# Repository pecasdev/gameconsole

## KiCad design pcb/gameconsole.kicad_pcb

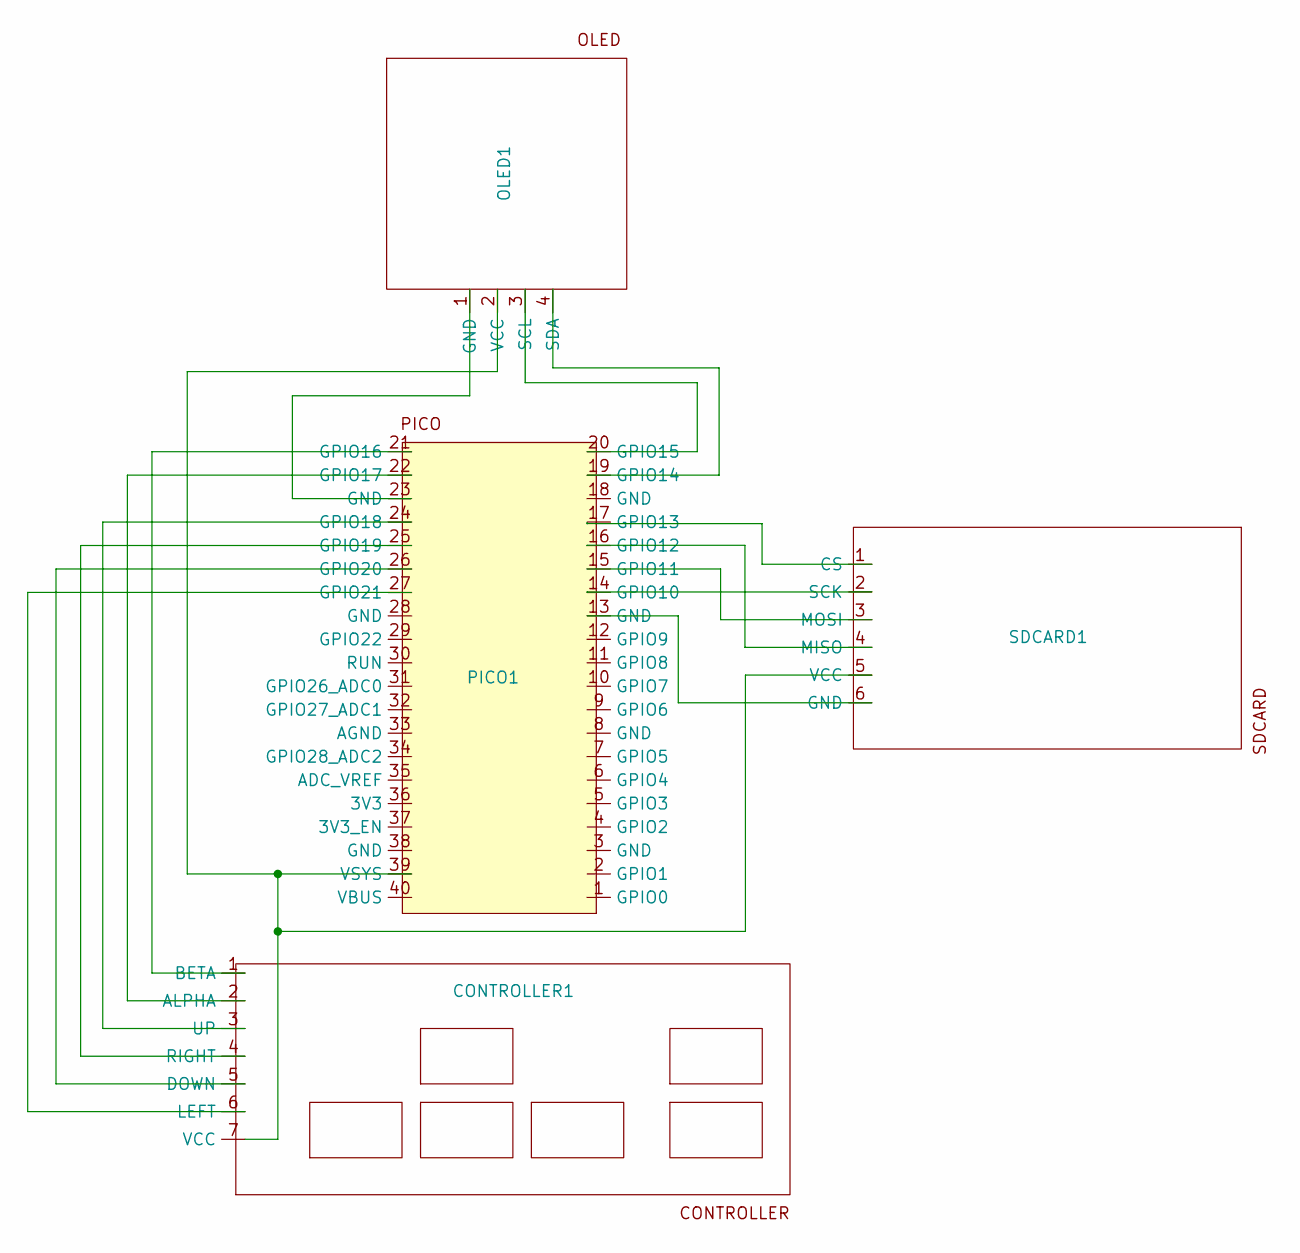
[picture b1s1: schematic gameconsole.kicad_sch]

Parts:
CONTROLLER1: controller_mount
OLED1: oled
PICO1: pico
SDCARD1: sdcard

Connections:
unnamed: CONTROLLER1.2 (ALPHA), PICO1.22 (GPIO17)
unnamed: CONTROLLER1.1 (BETA), PICO1.21 (GPIO16)
unnamed: CONTROLLER1.5 (DOWN), PICO1.26 (GPIO20)
unnamed: CONTROLLER1.6 (LEFT), PICO1.27 (GPIO21)
unnamed: CONTROLLER1.4 (RIGHT), PICO1.25 (GPIO19)
unnamed: CONTROLLER1.3 (UP), PICO1.24 (GPIO18)
unnamed: CONTROLLER1.7 (VCC), OLED1.2 (VCC), PICO1.39 (VSYS), SDCARD1.5 (VCC)
unnamed: OLED1.1 (GND), PICO1.23 (GND)
unnamed: OLED1.3 (SCL), PICO1.20 (GPIO15)
unnamed: OLED1.4 (SDA), PICO1.19 (GPIO14)
unnamed: PICO1.14 (GPIO10), SDCARD1.2 (SCK)
unnamed: PICO1.15 (GPIO11), SDCARD1.3 (MOSI)
unnamed: PICO1.16 (GPIO12), SDCARD1.4 (MISO)
unnamed: PICO1.17 (GPIO13), SDCARD1.1 (CS)
unnamed: PICO1.13 (GND), SDCARD1.6 (GND)

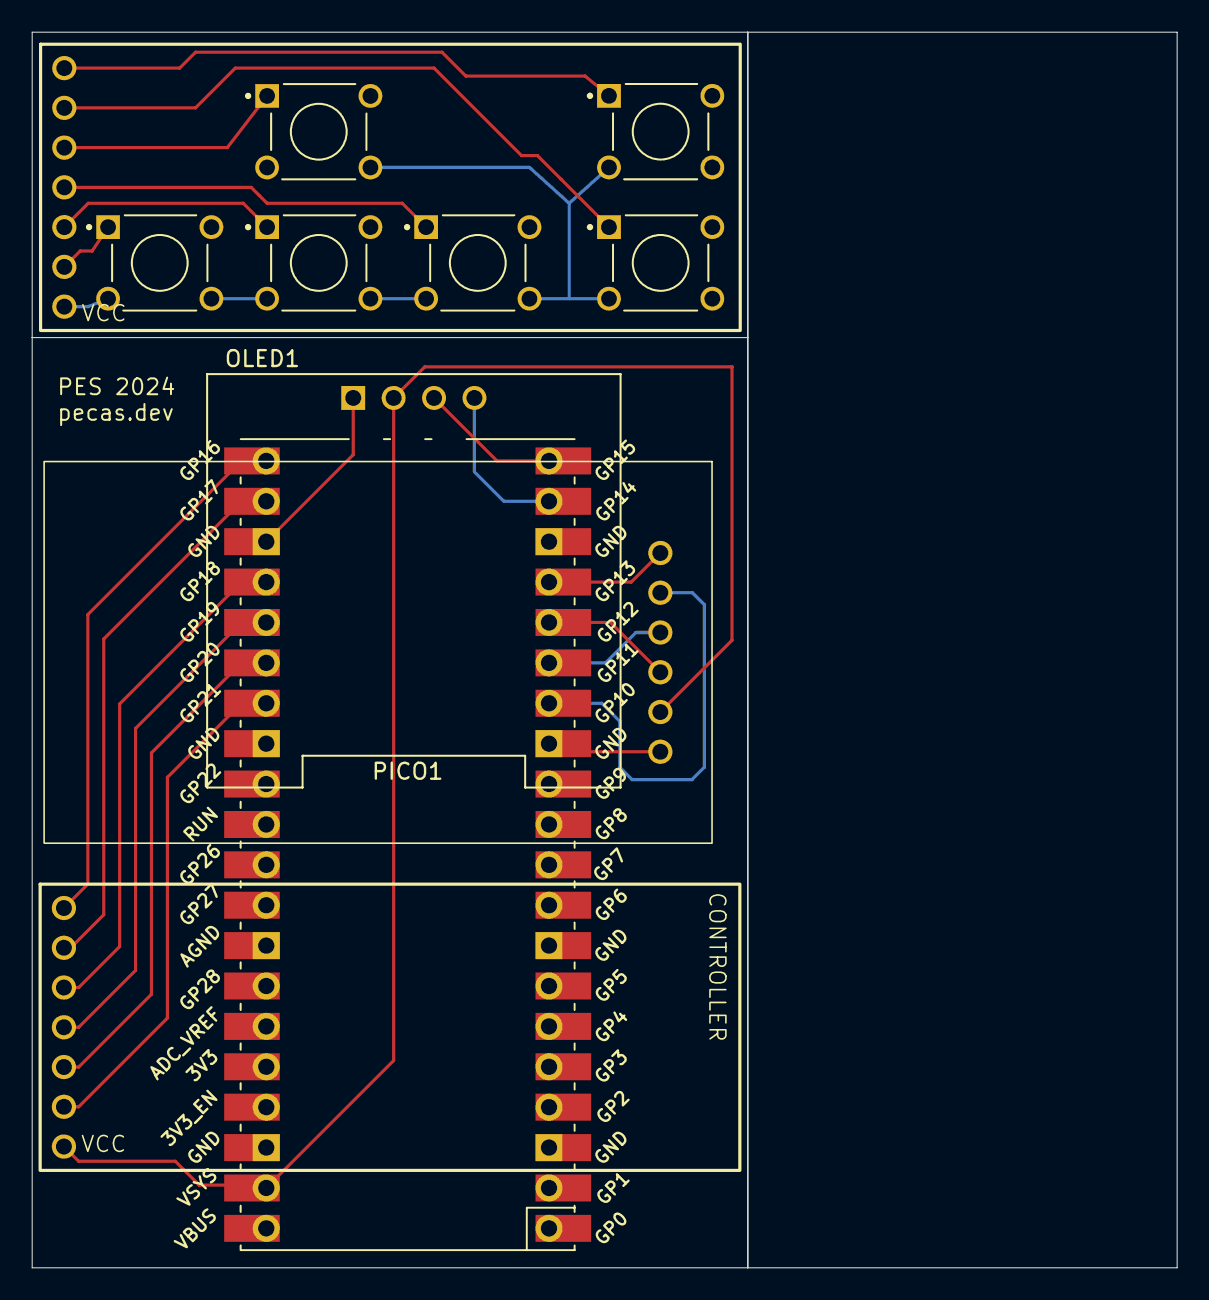
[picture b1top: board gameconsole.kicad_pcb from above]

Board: 2 copper layers, 72.0 x 77.7 mm, 5 parts (0 on the bottom side), 15 nets.

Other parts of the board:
U: controller

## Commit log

2024-07-15 Initial commit
    A dump of assorted files from last weekend's hackathon
2024-07-18 Remove individual inject folders
    Will move this to the root directory. Also moved original inject to examples folder
2024-07-18 Add snake to inject
2024-07-18 Create root init
    The plans for this is to have the emulator be the one-stop-shop for everything gameconsole. You can use it to flash the hardware or emulate the injection.
2024-07-18 Add flash_to_pico
2024-07-18 Remove draw_text from screen
    Font is currently handling this. Idk if this is the right way to implement it, I'll probably change it later
2024-07-18 Rewrite library
    - Engine has been made into a global object for ease of use
    - Some variables were made "private"
2024-07-18 Rewrite emulate button handling
    Button handling was heavily changed to try and speed up the emulator but there is still a noticable ~40ms delay that is not present on the hardware.
    Also inputs get occasionally dropped but I spent too much time on this to fix it. It's like 90% good now and it'll take 10 hours to get that last 10% so it's not a priority.
2024-07-18 Rename hardware __init__ -> main
    This is what pico uses so this change makes the naming more consistent
2024-07-18 Remove hardware debug statements
2024-07-19 Rewrite font
    Font should be way easier to use now. I also rewrote the font tool to match.
2024-07-19 Add InjectSelectMenu
    This will only be present in the hardware side. It gives the user the ability to choose what injection to load from the sd card
2024-07-19 Rewrite Font
2024-07-19 Move reaction example back to inject folder
    It should technically remain in the examples folder but I don't want 2 versions of the same code lingering around so I'll move it back to examples when I'm done
    I also added a small sprite usecase for the reaction game
2024-07-23 Rewrite reaction
    Now featuring new and improved sprites!
2024-07-23 Move font importing for emulation
2024-07-23 Add limitations
    I may update this later with my findings
2024-07-23 Remove pygame driver tick
    Since engine is doing tick capping, we don't need the pygame implementation
2024-07-23 Add button test example
2024-07-23 Add "professional" printing to main2
2024-07-23 Ignore more folders
    Tool input/output folders will be ignored. I think the inject folder should also be ignored just based on how frequently I update it. For the final version, I might put some dummy starter code there 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
2024-07-23 Add Alarm
2024-07-23 Rename v -> bitmap
2024-07-23 Improve injection copying
    Injection copying should now work recursively for nested folders and it should retry if copying fails (sometimes it does)
2024-07-23 Add FrameBufferAdaptor
    This only really exists so that sprites can be more efficiently drawn (the previous method took 5 seconds to blit on hardware)
2024-07-23 Untrack previously tracked files
2024-07-23 Fix HardwareState resetting
    This file is kind of a mess. I hope the convenience of a global variable is worth it
2024-07-23 Add "-" to font
    This replaces whatever godforsaken character I had in the bottom right before
2024-07-23 Change sprite_convert to strip extension when saving a sprite
2024-07-25 Reimplement pygame for emulator tick
    Apparently pygame doesn't like time.sleep
2024-07-25 Fix circular imports
    Python doesn't let you import a class to use for typing if that class imports the thing you're defining the type in (circular import). I almost miss java. I think there's a fix for this that involves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
2024-07-25 Add objects_of_class to Engine
2024-07-25 Rewrite snake
2024-07-29 Fix whitespace
2024-07-29 Fix import issues
2024-07-29 Fix tools module
2024-08-20 Rewrite __init__ to support tool scripts
2024-08-20 Add clear_pixel to Screen
2024-08-20 Add pcb files
2024-08-20 Make copy_file function safer
2024-08-20 Add returns to engine API
2024-08-20 Add util functions
2024-08-20 Add inject_select_menu
2024-08-20 Move hardware button pins to other side of pico
    Makes the PCB easier to engineer
2024-08-20 Add sprite loading
    This is mostly a hardware thing, it's to load spritedata into memory
2024-08-21 Add Tetris injection
2024-08-21 Rename examples -> published_injections
2024-08-21 Add flash_to_sd
2024-08-21 Fix sprite loading in reaction
2024-08-21 Clean up imports + comments
2024-08-27 Add debug information to engine_driver
2024-08-27 Move engine.now to its own file
2024-08-27 Add exception handling to engine_driver + main2
    Really should have done this a while ago lol
2024-08-27 Implement input event queue in engine_driver
    This should fix the issue of dropped inputs on low tickrate injections
2024-08-27 Add DEFAULT_SD_DRIVE flag to flash_to_sd
2024-08-27 Reorganize flash_to_pico lines alphabetically
2024-08-27 Rewrite snake injection to support new input event queue
2024-08-27 Add loadscreen
2024-08-27 Unignore input/output folders for tools
    It may actually be useful to show users how to use these folders with an example
2024-08-27 Add more characters to font
2024-08-27 Make loadscreen text fit on screen
2024-08-27 Add docs folder + README
2024-08-27 Move pcb folder to root directory
2024-08-27 Move hardware code to hardware_library folder
2024-08-27 Add comments
2024-08-27 Add remove_type_hints
    Previously didn't think this was even possible and I gave up on the idea. Huge implications because we can now typehint our python code without worrying about the syntax being unsupported in micropyt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
2024-08-27 Require typehint removal in pico/sd flashing
    Typehint removed code will go to a /dist folder which will be used by the flashing scripts
2024-08-27 Cleanup Font + write documentation
2024-08-28 Ignore obsidian workspace file
2024-08-28 Add medium font and large font
2024-08-28 Rename some dunderscore methods to single underscore
    Apparently dunderscore methods have some kind of implicit behavior that breaks the code
2024-08-28 Fix font_convert output file naming
2024-08-28 Add sd_copy_progress_bar
2024-08-28 Optimize ralph sprites in reaction injection
    Memory allocation error, hopefully not a recurring theme
2024-09-10 Remove PCB output contents
2024-09-10 Update PCB files
    I redesigned the overall footprint to be slimmer, as well as fixed several critical oversights like a component being upside down.
2024-09-10 Add case blender files
    Model files for the case that will enclose the PCB. These will be updated later
2024-09-10 Update all pins
    Reorganized the hardware pins to make PCB design more accessible
